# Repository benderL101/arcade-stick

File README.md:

# Arcade Stick

Firmware for DIY Bluetooth arcade sticks. One firmware runs on every stick: each stick's colour (and so its Bluetooth name) and wiring are set in its own menu. Each one uses:
- a Freenove ESP32-S3 2.8" board (FNK0104) with an MCP23017 I/O expander
- a Sanwa JLF stick, 6 × 30 mm and 3 × 24 mm buttons, and the board's speaker

They're built for SteamOS and RetroArch over Bluetooth.

The full manual is in [docs/MANUAL.md](docs/MANUAL.md). It covers wiring, flashing, the menu, shortcuts, the Moves page and sounds.

## Updating a stick

Download files from the [latest release](../../releases/latest).

| Way | What to do |
|---|---|
| **Check for update** (v2.3+) | On the stick: **Menu → Check for update → B4**. It finds the newest release here and installs it. You need to save your home Wi-Fi once first (see the manual). |
| Wi-Fi from a phone | **Menu → Wi-Fi update**, join `ArcadeStick-<colour>` (password `arcadestick`), open http://192.168.4.1, upload the `_wifi.bin` file. |
| USB cable | **Menu → USB update**, then flash the `_usb.bin` file at address 0x0. |

The same files work on every stick. New sticks use the standard wiring in the manual.

## Making a release

1. Bump `FW_VERSION` in `src/main.cpp`, e.g. `"2.6"`, and push.
2. Create a GitHub release tagged `v2.6`. That's all: the **Build release files** action (`.github/workflows/release.yml`) builds the firmware, runs the tests and attaches the four `.bin` files to the release within a few minutes.

To build by hand instead: `tools/make_release.sh` writes the four files to `release/` (`_usb`, `_wifi`, and the `_red_wifi` / `_blue_wifi` copies for sticks still on v2.3).

The sticks compare the release tag with their own version. v2.4+ download the asset ending in `_wifi.bin`. Sticks still on v2.3 look for `_red_wifi.bin` / `_blue_wifi.bin`, which is why the release keeps those copies.

## Layout

| Path | What |
|---|---|
| `src/main.cpp` | Firmware: input, Bluetooth/USB gamepad, screen, menu, sound, updates |
| `src/moves.h` | Fighting game move lists and the move recogniser |
| `test/test_moves.cpp` | Host tests for the move recogniser and trainer: `g++ -std=c++17 -Isrc test/test_moves.cpp && ./a.out` |
| `test/test_gamelink.py` | Host tests for Game link (RetroArch replies, labels file): `python3 test/test_gamelink.py` |
| `platformio.ini` | Builds `arcade_stick` |
| `tools/make_release.sh` | Builds the four release files |
| `hardware/io-board/` | I/O board for building more sticks: JLCPCB files, parts list, soldering and wiring guide |

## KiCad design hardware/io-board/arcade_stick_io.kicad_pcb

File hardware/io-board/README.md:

# Arcade Stick I/O board v1.0

A small through-hole board that replaces the loose MCP23017 module and its hand-soldered wiring. Every button and stick direction gets its own screw terminal (signal + GND). The terminals are labelled and laid out to the firmware's **standard wiring**, so a new stick works with **Menu → Wiring → Standard** (the default).

| Front | Back |
|---|---|
|  |  |

- Size: **97 × 49.5 mm**, 2 layers, 3 × M3 mounting holes. That's under 10 × 10 cm, so it gets JLCPCB's cheapest price.
- Everything is through-hole, so it can be soldered with an ordinary iron.
- Tallest parts: the screw terminals (about 10 mm) and the chip in its socket (about 8 mm). Allow roughly 12 mm above the board inside the case.

## Ordering from JLCPCB

1. Go to jlcpcb.com, click **Order now** and upload `ArcadeStick_IO_v1.0_JLCPCB.zip`. Don't unzip it.
2. Leave the defaults: 2 layers, 1.6 mm thick, quantity 5. It reads the size by itself (97 × 49.5 mm).
3. Pick any colour. Green is quickest and cheapest.
4. Optional: **Remove order number → Yes** (small extra fee). Otherwise JLCPCB prints a small code somewhere on the board.
5. Don't add assembly (PCBA). You'll solder the parts yourself.
6. At checkout, the cheapest shipping (Global Standard Direct Line) takes a couple of weeks. DHL is faster but costs more.

## Parts (per board)

| Ref | Part | Qty | Notes |
|---|---|---|---|
| U1 | MCP23017-E/SP (DIP-28, through-hole) | 1 | e.g. Core Electronics, element14 |
| U1 socket | 28-pin **narrow** (0.3") IC socket | 1 | So the chip can be swapped |
| JT1–JT7, JB1–JB7 | 2-way PCB screw terminal, 5 mm / 5.08 mm pitch | 14 | e.g. Jaycar HM3172 |
| J1 | 4-pin 2.54 mm male header | 1 | For the Freenove I2C cable's Dupont ends |
| J2 | 3-pin 2.54 mm male header | 1 | Optional: spare interrupt pins for later |
| R1, R2 | 4.7 kΩ resistor, 1/4 W | 2 | I2C pull-ups. Fit them: harmless if the Freenove board has its own |
| C1 | 100 nF ceramic capacitor (2.5 mm lead spacing) | 1 | Decoupling |

## Soldering

Go from lowest to tallest:
1. R1, R2 (R2 stands upright) and C1.
2. The 28-pin socket. Its **notch goes on the left**, matching the half-circle on the board outline.
3. J1 (and J2 if you want it).
4. The 14 screw terminals. Put the wire openings facing the **board edge**, where the labels are.
5. Push the MCP23017 into the socket, **notch on the left**. Pin 1 is the square pad, bottom left.

## Wiring

- **J1 → Freenove I2C port:** 3V3 → 3V3, GND → GND, SCL → SCL, SDA → SDA. Each pin is labelled on the board.
- **Buttons and stick:** each wire goes to the terminal with its name. Each terminal has a GND screw beside it. With a daisy-chained ground you only need one GND connection; the rest can stay empty.
  - Top row: SELECT, START, HOME, UP, DOWN, RIGHT, LEFT.
  - Bottom row: B3, B2, B1, B6, B5, B4, EX. These are in chip-pin order. B1–B3 are the top row of buttons, left to right, and B4–B6 the bottom row.
- **Firmware:** leave **Menu → Wiring** on **Standard**. Then open **Menu → Input test** and press every button and direction to check each one lights up correctly.

## Checks done on this design

- **KiCad design-rule check:** 0 violations, 0 unconnected pads. The rules are 0.25 mm clearance, 0.4 mm signal traces and 0.5 mm power traces.
- **`check_board.py`:** confirms these against the finished board file:
  - every MCP23017 pin against Microchip's datasheet pinout
  - every terminal against `MCP_BIT_STD` in `src/main.cpp`
  - the exact pad list of every net, and the label beside each terminal
- **Gerber renders:** the images above are drawn from the Gerber files themselves. Drill count: 34 × 0.8 mm, 7 × 1.0 mm, 28 × 1.52 mm and 3 × 3.2 mm (NPTH).
- **Not yet built:** the first boards are the real test.

## Remaking the files

```bash
python3 make_board.py           # writes arcade_stick_io.kicad_pcb (KiCad 7)
python3 fill_drc.py arcade_stick_io.kicad_pcb   # fills the ground pours, writes the DRC report
python3 check_board.py          # netlist / firmware / label checks
kicad-cli pcb export gerbers -o gerbers/ -l F.Cu,B.Cu,F.Mask,B.Mask,F.Silkscreen,B.Silkscreen,Edge.Cuts --no-x2 --subtract-soldermask arcade_stick_io.kicad_pcb
kicad-cli pcb export drill -o gerbers/ --format excellon --drill-origin absolute --excellon-units mm --excellon-separate-th arcade_stick_io.kicad_pcb
```
Set `KICAD7_FOOTPRINT_DIR=/usr/share/kicad/footprints` if KiCad's library table can't find the footprints.

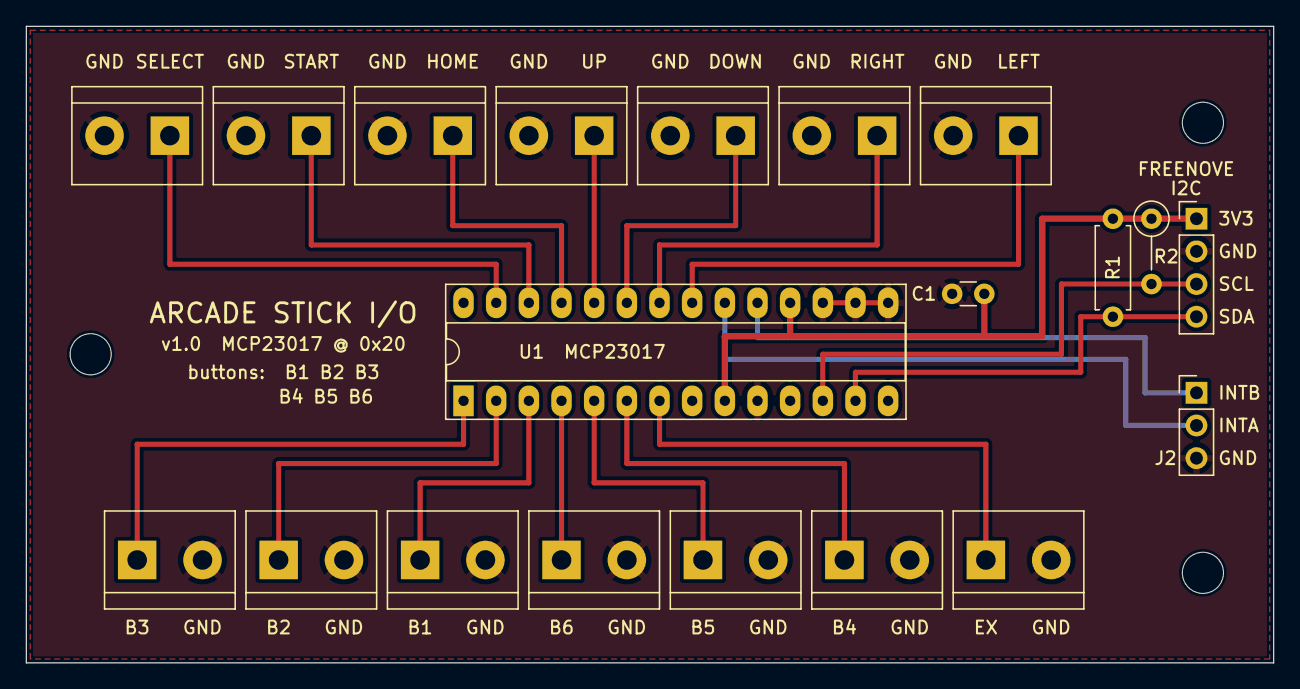
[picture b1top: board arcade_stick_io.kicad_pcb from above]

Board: 2 copper layers, 97.0 x 49.5 mm, 23 parts (0 on the bottom side), 20 nets.

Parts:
C1: 100nF; C_Disc_D3.0mm_W1.6mm_P2.50mm
H1, H2, H3: MountingHole_3.2mm_M3
J1: I2C to Freenove; PinHeader_1x04_P2.54mm_Vertical
J2: INT (spare); PinHeader_1x03_P2.54mm_Vertical
JB1, JB2, JB3, JB4, JB5, JB6, JB7: Screw terminal 2P 5.08; TerminalBlock_bornier-2_P5.08mm
JT1, JT2, JT3, JT4, JT5, JT6, JT7: Screw terminal 2P 5.08; TerminalBlock_bornier-2_P5.08mm
R1: 4.7k; R_Axial_DIN0207_L6.3mm_D2.5mm_P7.62mm_Horizontal
R2: 4.7k; R_Axial_DIN0207_L6.3mm_D2.5mm_P5.08mm_Vertical
U1: MCP23017-E/SP; DIP-28_W7.62mm_Socket_LongPads

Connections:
3V3: C1.1, J1.1, R1.1, R2.1, U1.9, U1.18
B1: JB3.1, U1.3
B2: JB2.1, U1.2
B3: JB1.1, U1.1
B4: JB6.1, U1.6
B5: JB5.1, U1.5
B6: JB4.1, U1.4
DOWN: JT5.1, U1.23
EX: JB7.1, U1.7
GND: C1.2, J1.2, J2.3, JB1.2, JB2.2, JB3.2, JB4.2, JB5.2, JB6.2, JB7.2, JT1.2, JT2.2, JT3.2, JT4.2, JT5.2, JT6.2, JT7.2, U1.10, U1.15, U1.16, U1.17
HOME: JT3.1, U1.25
INTA: J2.2, U1.20
INTB: J2.1, U1.19
LEFT: JT7.1, U1.21
RIGHT: JT6.1, U1.22
SCL: J1.3, R2.2, U1.12
SDA: J1.4, R1.2, U1.13
SELECT: JT1.1, U1.27
START: JT2.1, U1.26
UP: JT4.1, U1.24
